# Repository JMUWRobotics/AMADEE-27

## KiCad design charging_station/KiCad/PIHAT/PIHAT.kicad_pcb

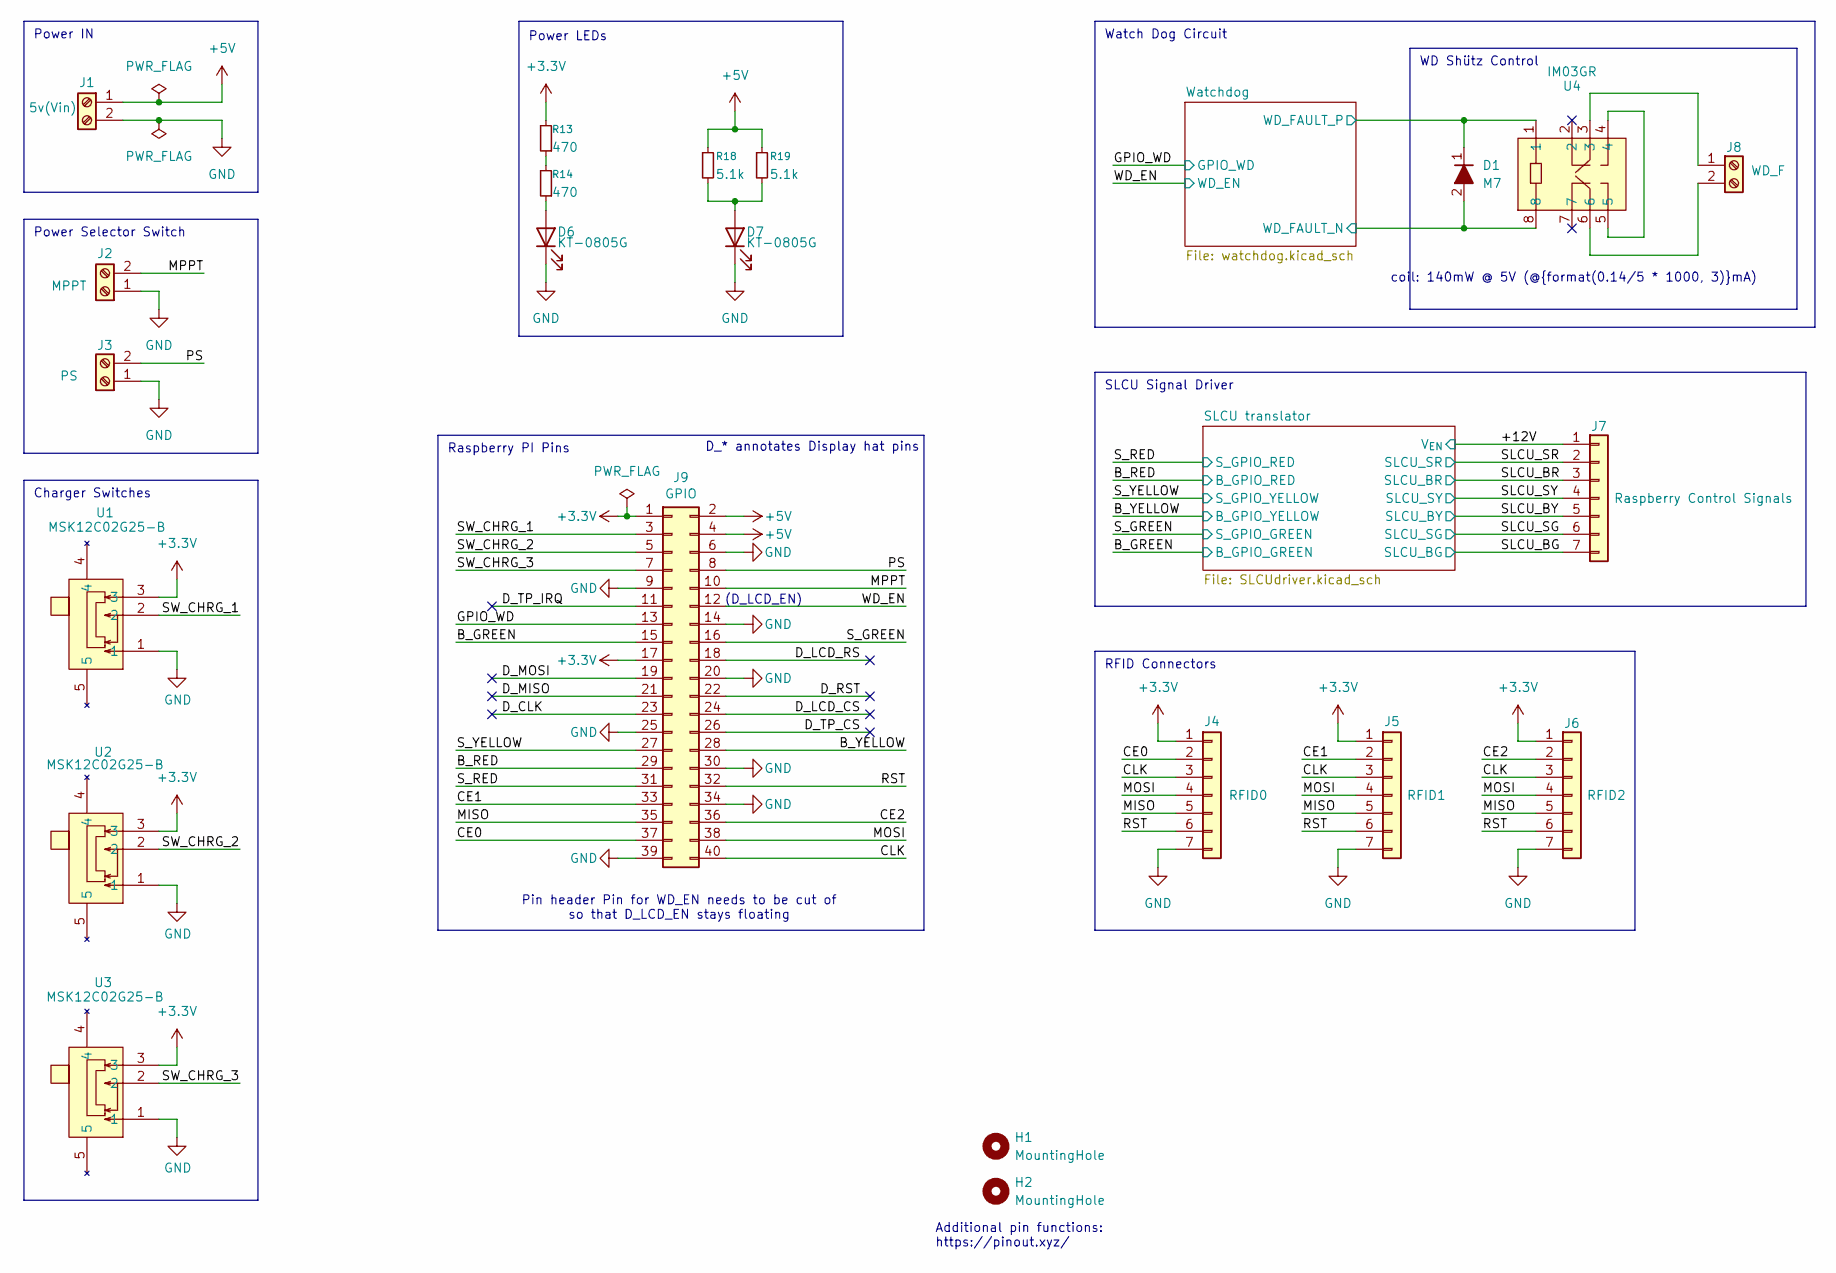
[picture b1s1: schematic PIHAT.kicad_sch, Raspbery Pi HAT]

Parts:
D1: M7; D_SMA; MPN M7; LCSC Part C95872
D6, D7: KT-0805G; LED_0805_2012Metric; MPN KT-0805G; LCSC Part C2297
H1: MountingHole; MountingHole_2.2mm_M2_DIN965_Pad
H2: MountingHole; MountingHole_2.5mm_Pad
J1: 5v(Vin); TerminalBlock_Phoenix_PT-1,5-2-5.0-H_1x02_P5.00mm_Horizontal; MPN 1935161; LCSC Part C3819953
J2: MPPT; TerminalBlock_Phoenix_PT-1,5-2-5.0-H_1x02_P5.00mm_Horizontal; MPN 1935161; LCSC Part C3819953
J3: PS; TerminalBlock_Phoenix_PT-1,5-2-5.0-H_1x02_P5.00mm_Horizontal; MPN 1935161; LCSC Part C3819953
J4: RFID0; JST_XH_S7B-XH-A_1x07_P2.50mm_Horizontal; MPN S7B-XH-A(LF)(SN); LCSC Part C157916
J5: RFID1; JST_XH_S7B-XH-A_1x07_P2.50mm_Horizontal; MPN S7B-XH-A(LF)(SN); LCSC Part C157916
J6: RFID2; JST_XH_S7B-XH-A_1x07_P2.50mm_Horizontal; MPN S7B-XH-A(LF)(SN); LCSC Part C157916
J7: Raspberry Control Signals; JST_XH_S7B-XH-A_1x07_P2.50mm_Horizontal; MPN S7B-XH-A(LF)(SN); LCSC Part C157916
J8: WD_F; TerminalBlock_Phoenix_PT-1,5-2-5.0-H_1x02_P5.00mm_Horizontal; MPN 1935161; LCSC Part C3819953
J9: GPIO; PinSocket_2x20_P2.54mm_Vertical; MPN SSQ-120-03-T-D; LCSC C6235776
R13, R14: 470; R_0603_1608Metric; LCSC C23179
R18, R19: 5.1k; R_0603_1608Metric; LCSC C17414
U1, U2, U3: MSK12C02G25-B; SW-SMD_MSK12C02G25-B; MPN MSK12C02G25-B; LCSC Part C22435663
U4: IM03GR; RELAY-SMD_IMXXGR; MPN IM03GR; LCSC Part C2153100

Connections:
+3.3V: J4.1, J5.1, J6.1, J9.1, J9.17, R13.2, U1.3, U2.3, U3.3; also elsewhere on the board
+5V: J1.1, J9.2, J9.4, R18.1, R19.1; also elsewhere on the board
/+12V: J7.1; also elsewhere on the board
/B_GREEN: J9.15; also elsewhere on the board
/B_RED: J9.29; also elsewhere on the board
/B_YELLOW: J9.28; also elsewhere on the board
/CE0: J4.2, J9.37
/CE1: J5.2, J9.33
/CE2: J6.2, J9.36
/CLK: J4.3, J5.3, J6.3, J9.40
/D_CLK: J9.23
/D_LCD_CS: J9.24
/D_LCD_RS: J9.18
/D_MISO: J9.21
/D_MOSI: J9.19
/D_RST: J9.22
/D_TP_CS: J9.26
/D_TP_IRQ: J9.11
/GPIO_WD: J9.13; also elsewhere on the board
/MISO: J4.5, J5.5, J6.5, J9.35
/MOSI: J4.4, J5.4, J6.4, J9.38
/MPPT: J2.2, J9.10
/PS: J3.2, J9.8
/RST: J4.6, J5.6, J6.6, J9.32
/SLCU_BG: J7.7; also elsewhere on the board
/SLCU_BR: J7.3; also elsewhere on the board
/SLCU_BY: J7.5; also elsewhere on the board
/SLCU_SG: J7.6; also elsewhere on the board
/SLCU_SR: J7.2; also elsewhere on the board
/SLCU_SY: J7.4; also elsewhere on the board
/SW_CHRG_1: J9.3, U1.2
/SW_CHRG_2: J9.5, U2.2
/SW_CHRG_3: J9.7, U3.2
/S_GREEN: J9.16; also elsewhere on the board
/S_RED: J9.31; also elsewhere on the board
/S_YELLOW: J9.27; also elsewhere on the board
/WD_EN: J9.12; also elsewhere on the board
/Watchdog/WD_FAULT_N: D1.2 (A), U4.8; also elsewhere on the board
/Watchdog/WD_FAULT_P: D1.1 (K), U4.1; also elsewhere on the board
GND: D6.1 (K), D7.1 (K), J1.2, J2.1, J3.1, J4.7, J5.7, J6.7, J9.6, J9.9, J9.14, J9.20, J9.25, J9.30, J9.34, J9.39, U1.1, U2.1, U3.1; also elsewhere on the board
unnamed: D6.2 (A), R14.1
unnamed: D7.2 (A), R18.2, R19.2
unnamed: J8.1, U4.3
unnamed: J8.2, U4.6
unnamed: R13.1, R14.2
unnamed: U4.4, U4.5

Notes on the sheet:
Raspberry PI Pins
(D_LCD_EN)
Additional pin functions: https://pinout.xyz/
SLCU Signal Driver
RFID Connectors
WD Shütz Control
Pin header Pin for WD_EN needs to be cut of so that D_LCD_EN stays floating
Power Selector Switch
Watch Dog Circuit
Power LEDs
Charger Switches
Power IN
coil: 140mW @ 5V (@{format(0.14/5 * 1000, 3)}mA)
D_* annotates Display hat pins

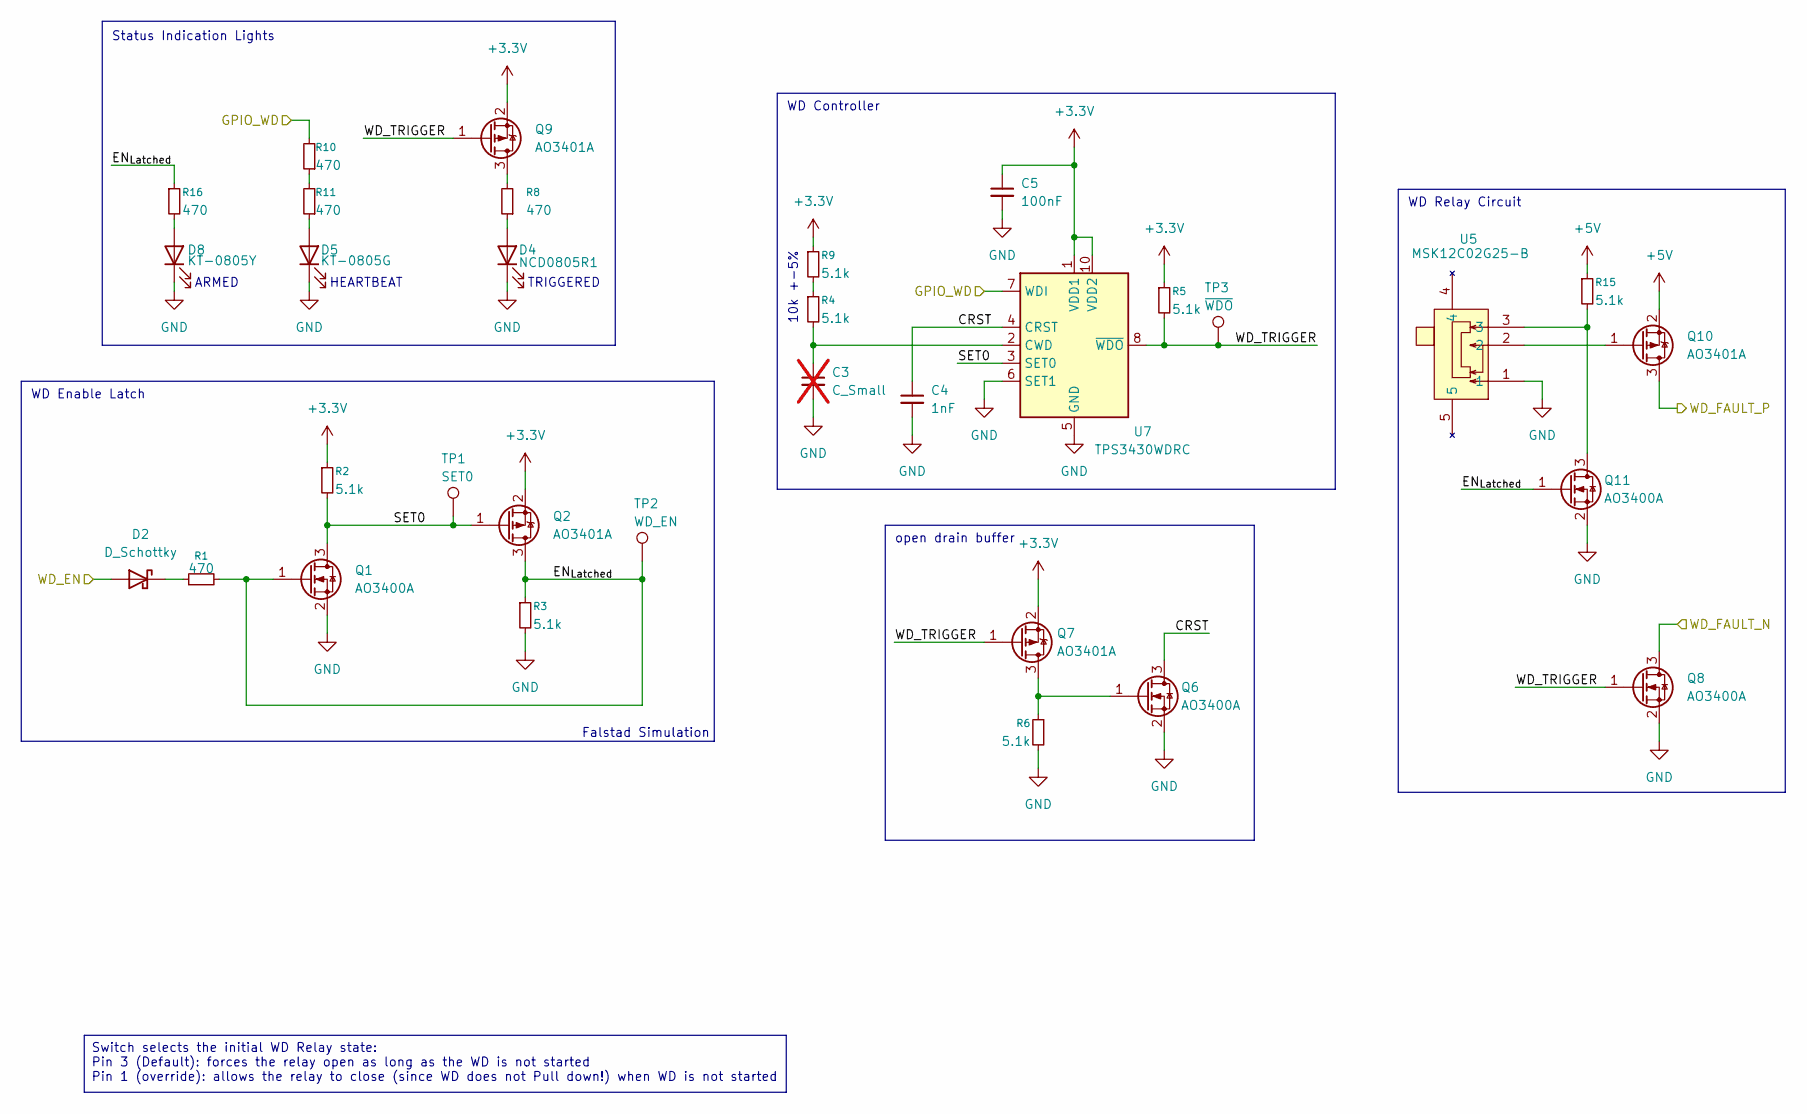
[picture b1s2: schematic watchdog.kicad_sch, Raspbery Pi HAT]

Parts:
C3: C_Small; C_0805_2012Metric_Pad1.18x1.45mm_HandSolder; not fitted
C4: 1nF; C_0603_1608Metric
C5: 100nF; C_0603_1608Metric; LCSC Part C14663
D2: D_Schottky; D_SOD-323
D4: NCD0805R1; LED_0805_2012Metric; MPN NCD0805R1; LCSC Part C84256
D5: KT-0805G; LED_0805_2012Metric; MPN KT-0805G; LCSC Part C2297
D8: KT-0805Y; LED_0805_2012Metric; MPN KT-0805Y; LCSC Part C2296
Q1, Q6, Q8, Q11: AO3400A; SOT-23; MPN AO3400A; LCSC Part C15127
Q2, Q7, Q9, Q10: AO3401A; SOT-23; MPN AO3401A; LCSC Part C15127
R1, R8, R10, R11, R16: 470; R_0603_1608Metric; LCSC C23179
R2, R3, R4, R5, R6, R9, R15: 5.1k; R_0603_1608Metric; LCSC C17414
TP1: SET0; TestPoint_Pad_D1.0mm
TP2: WD_EN; TestPoint_Pad_D1.0mm
TP3: ~{WDO}; TestPoint_Pad_D1.0mm
U5: MSK12C02G25-B; SW-SMD_MSK12C02G25-B; MPN MSK12C02G25-B; LCSC Part C22435663
U7: TPS3430WDRC; VSON-10-1EP_3x3mm_P0.5mm_EP1.65x2.4mm

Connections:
+3.3V: C5.1, Q2.2 (S), Q7.2 (S), Q9.2 (S), R2.1, R5.1, R9.1, U7.1 (VDD1), U7.10 (VDD2); also elsewhere on the board
+5V: Q10.2 (S), R15.1; also elsewhere on the board
/GPIO_WD: R10.2, U7.7 (WDI); also elsewhere on the board
/WD_EN: D2.2 (A); also elsewhere on the board
/Watchdog/CRST: C4.1, Q6.3 (D), U7.4 (CRST)
/Watchdog/EN_{Latched}: Q1.1 (G), Q2.3 (D), Q11.1 (G), R1.2, R3.1, R16.1, TP2.1 (1_1)
/Watchdog/SET0: Q1.3 (D), Q2.1 (G), R2.2, TP1.1 (1_1), U7.3 (SET0)
/Watchdog/WD_FAULT_N: Q8.3 (D); also elsewhere on the board
/Watchdog/WD_FAULT_P: Q10.3 (D); also elsewhere on the board
/Watchdog/WD_TRIGGER: Q7.1 (G), Q8.1 (G), Q9.1 (G), R5.2, TP3.1 (1_1), U7.8 (~WDO)
GND: C3.2, C4.2, C5.2, D4.1 (K), D5.1 (K), D8.1 (K), Q1.2 (S), Q6.2 (S), Q8.2 (S), Q11.2 (S), R3.2, R6.2, U5.1, U7.5 (GND), U7.6 (SET1), U7.11 (GND); also elsewhere on the board
unnamed: D2.1 (K), R1.1
unnamed: D4.2 (A), R8.1
unnamed: D5.2 (A), R11.1
unnamed: D8.2 (A), R16.2
unnamed: Q6.1 (G), Q7.3 (D), R6.1
unnamed: Q9.3 (D), R8.2
unnamed: Q10.1 (G), U5.2
unnamed: Q11.3 (D), R15.2, U5.3
unnamed: R4.1, R9.2
unnamed: R10.1, R11.2
unnamed: C3.1, R4.2, U7.2 (CWD)

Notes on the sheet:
HEARTBEAT
open drain buffer
10k +-5%
Falstad Simulation
WD Enable Latch
TRIGGERED
Status Indication Lights
ARMED
WD Controller
WD Relay Circuit
Switch selects the initial WD Relay state: Pin 3 (Default): forces the relay open as long as the WD is not started Pin 1 (override): allows the relay to close (since WD does not Pull down!) when WD is not started

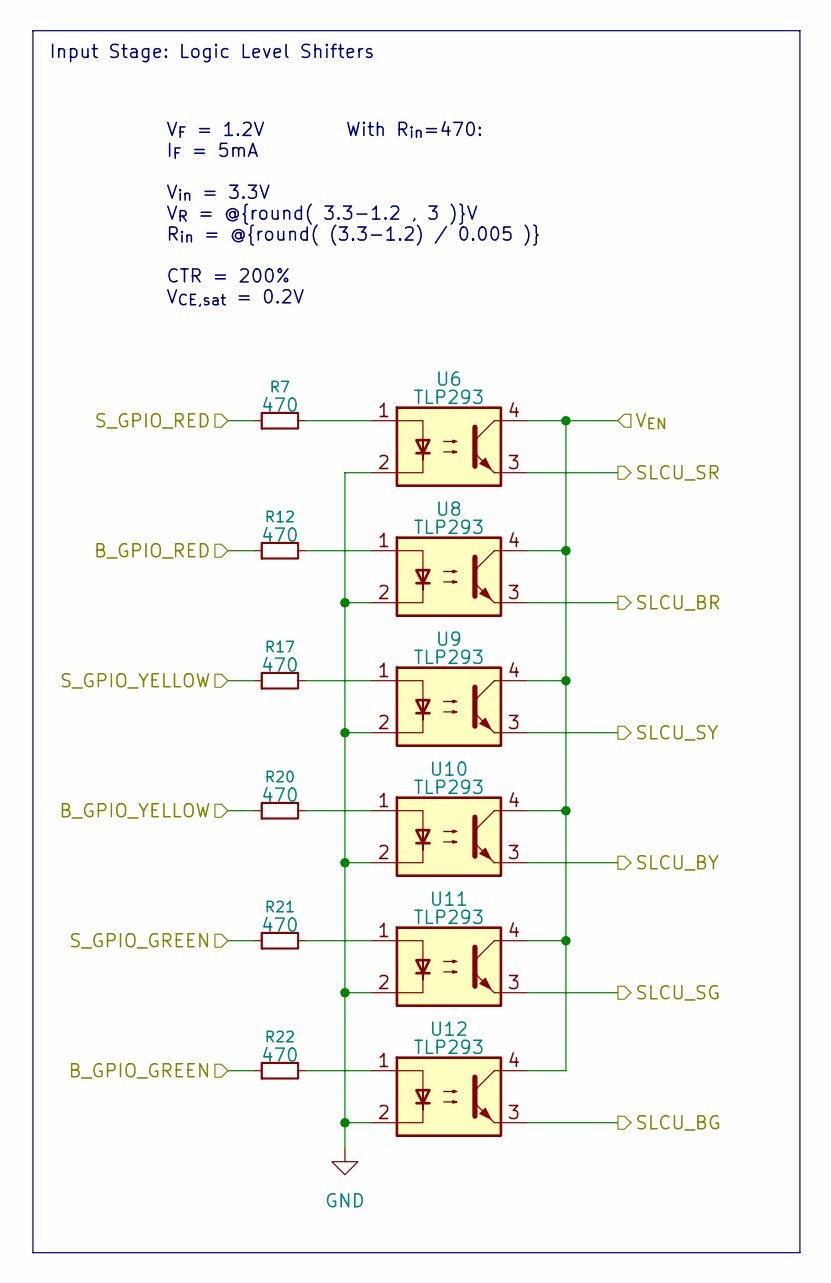
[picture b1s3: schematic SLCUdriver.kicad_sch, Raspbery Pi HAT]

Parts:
R7, R12, R17, R20, R21, R22: 470; R_0603_1608Metric; LCSC C23179
U6, U8, U9, U10, U11, U12: TLP293; SOIC-4_4.55x2.6mm_P1.27mm; MPN TLP293(BLL-TPL,E; LCSC C3008594

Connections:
/+12V: U6.4, U8.4, U9.4, U10.4, U11.4, U12.4; also elsewhere on the board
/B_GREEN: R22.1; also elsewhere on the board
/B_RED: R12.1; also elsewhere on the board
/B_YELLOW: R20.1; also elsewhere on the board
/SLCU_BG: U12.3; also elsewhere on the board
/SLCU_BR: U8.3; also elsewhere on the board
/SLCU_BY: U10.3; also elsewhere on the board
/SLCU_SG: U11.3; also elsewhere on the board
/SLCU_SR: U6.3; also elsewhere on the board
/SLCU_SY: U9.3; also elsewhere on the board
/S_GREEN: R21.1; also elsewhere on the board
/S_RED: R7.1; also elsewhere on the board
/S_YELLOW: R17.1; also elsewhere on the board
GND: U6.2, U8.2, U9.2, U10.2, U11.2, U12.2; also elsewhere on the board
unnamed: R7.2, U6.1
unnamed: R12.2, U8.1
unnamed: R17.2, U9.1
unnamed: R20.2, U10.1
unnamed: R21.2, U11.1
unnamed: R22.2, U12.1

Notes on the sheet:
With R_{in}=470:
V_{F} = 1.2V I_{F} = 5mA V_{in} = 3.3V V_{R} = @{round( 3.3-1.2 , 3 )}V R_{in} = @{round( (3.3-1.2) / 0.005 )} CTR = 200% V_{CE,sat} = 0.2V
Input Stage: Logic Level Shifters

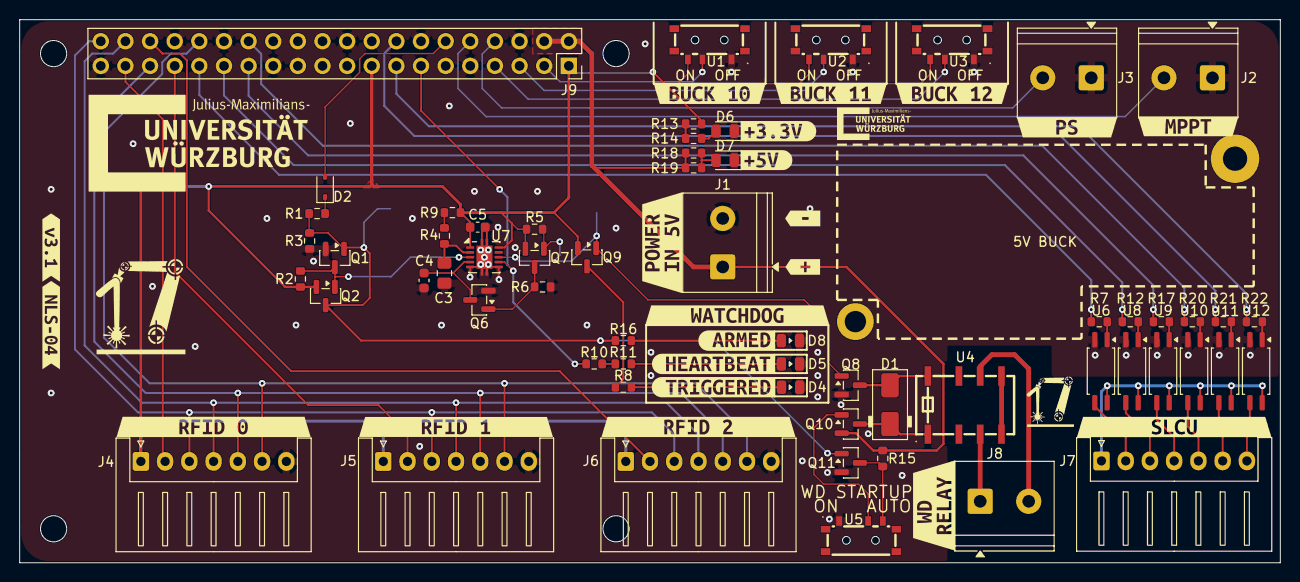
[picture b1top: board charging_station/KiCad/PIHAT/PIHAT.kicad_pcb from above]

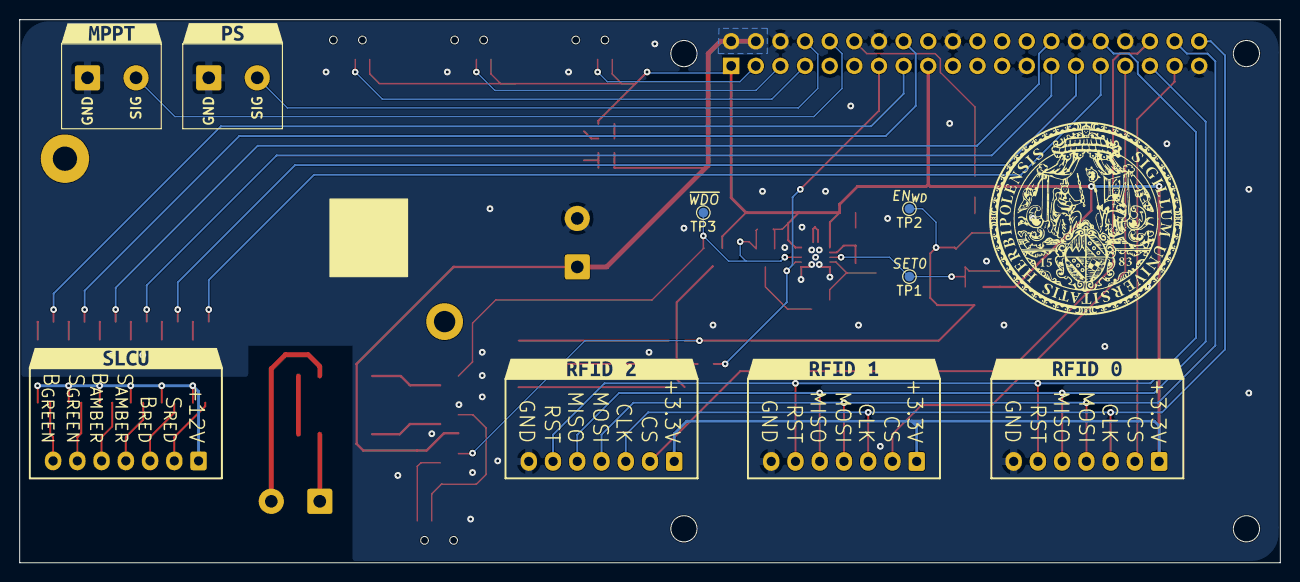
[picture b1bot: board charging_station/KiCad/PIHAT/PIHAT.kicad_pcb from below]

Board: 2 copper layers, 130.0 x 56.0 mm, 97 parts (13 on the bottom side), 59 nets.

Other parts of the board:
MH1, MH2, MH3, MH4: MountingHole_2.7mm_M2.5
kibuzzard-6AD53C3D: G***; kibuzzard-6AD53C3D
kibuzzard-6AD53C20, kibuzzard-6AD53C20#2: G***; kibuzzard-6AD53C20
kibuzzard-6AD53C43: G***; kibuzzard-6AD53C43
kibuzzard-6AD53C84: G***; kibuzzard-6AD53C84
kibuzzard-6AD53CF1: G***; kibuzzard-6AD53CF1
kibuzzard-6AD53D49: G***; kibuzzard-6AD53D49
kibuzzard-6AD53DF3: G***; kibuzzard-6AD53DF3
kibuzzard-6AD53E3A: G***; kibuzzard-6AD53E3A
kibuzzard-6AD53E40: G***; kibuzzard-6AD53E40
kibuzzard-6AD530C8: G***; kibuzzard-6AD530C8
kibuzzard-6AD530EA: G***; kibuzzard-6AD530EA
kibuzzard-6AD537E7: G***; kibuzzard-6AD537E7
kibuzzard-6AD540AE: G***; kibuzzard-6AD540AE
kibuzzard-6AD541D1: G***; kibuzzard-6AD541D1
kibuzzard-6AD543B1: G***; kibuzzard-6AD543B1
kibuzzard-6AD543B7: G***; kibuzzard-6AD543B7
kibuzzard-6AD554A5: G***; kibuzzard-6AD554A5
kibuzzard-6AD5310E: G***; kibuzzard-6AD5310E
kibuzzard-6AD5403C: G***; kibuzzard-6AD5403C
kibuzzard-6AD54089: G***; kibuzzard-6AD54089
kibuzzard-6AF5E61E: G***; kibuzzard-6AF5E61E
kibuzzard-6AF5E623: G***; kibuzzard-6AF5E623
kibuzzard-6AF5EA3F: G***; kibuzzard-6AF5EA3F
kibuzzard-6AF5F1CD: G***; kibuzzard-6AF5F1CD
kibuzzard-6AF5F1D2: G***; kibuzzard-6AF5F1D2
kibuzzard-6AF35593: G***; kibuzzard-6AF35593

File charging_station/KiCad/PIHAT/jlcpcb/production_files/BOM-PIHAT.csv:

Comment,Designator,Footprint,LCSC,Quantity
100nF,C5,C_0603_1608Metric,C14663,1
1nF,C4,C_0603_1608Metric,C1588,1
470,"R1,R10,R11,R12,R13,R14,R16,R17,R20,R21,R22,R7,R8",R_0603_1608Metric,C23179,13
5.1k,"R15,R18,R19,R2,R3,R4,R5,R6,R9",R_0603_1608Metric,C23186,9
5v(Vin),J1,"TerminalBlock_Phoenix_PT-1,5-2-5.0-H_1x02_P5.00mm_Horizontal",C3819953,1
AO3400A,"Q1,Q11,Q6,Q8",SOT-23,C20917,4
AO3401A,"Q10,Q2,Q7,Q9",SOT-23,C15127,4
D_Schottky,D2,D_SOD-323,C7420360,1
GPIO,J9,PinSocket_2x20_P2.54mm_Vertical,C6235776,1
IM03GR,U4,RELAY-SMD_IMXXGR,C2153100,1
KT-0805G,"D5,D6,D7",LED_0805_2012Metric,C2297,3
KT-0805Y,D8,LED_0805_2012Metric,C2296,1
M7,D1,D_SMA,C95872,1
MPPT,J2,"TerminalBlock_Phoenix_PT-1,5-2-5.0-H_1x02_P5.00mm_Horizontal",C3819953,1
MSK12C02G25-B,"U1,U2,U3,U5",SW-SMD_MSK12C02G25-B,C22435663,4
NCD0805R1,D4,LED_0805_2012Metric,C84256,1
PS,J3,"TerminalBlock_Phoenix_PT-1,5-2-5.0-H_1x02_P5.00mm_Horizontal",C3819953,1
RFID0,J4,JST_XH_S7B-XH-A_1x07_P2.50mm_Horizontal,C157916,1
RFID1,J5,JST_XH_S7B-XH-A_1x07_P2.50mm_Horizontal,C157916,1
RFID2,J6,JST_XH_S7B-XH-A_1x07_P2.50mm_Horizontal,C157916,1
Raspberry Control Signals,J7,JST_XH_S7B-XH-A_1x07_P2.50mm_Horizontal,C157916,1
TLP293,"U10,U11,U12,U6,U8,U9",SOIC-4_4.55x2.6mm_P1.27mm,C3008594,6
TPS3430WDRC,U7,VSON-10-1EP_3x3mm_P0.5mm_EP1.65x2.4mm,C2870545,1
WD_F,J8,"TerminalBlock_Phoenix_PT-1,5-2-5.0-H_1x02_P5.00mm_Horizontal",C3819953,1

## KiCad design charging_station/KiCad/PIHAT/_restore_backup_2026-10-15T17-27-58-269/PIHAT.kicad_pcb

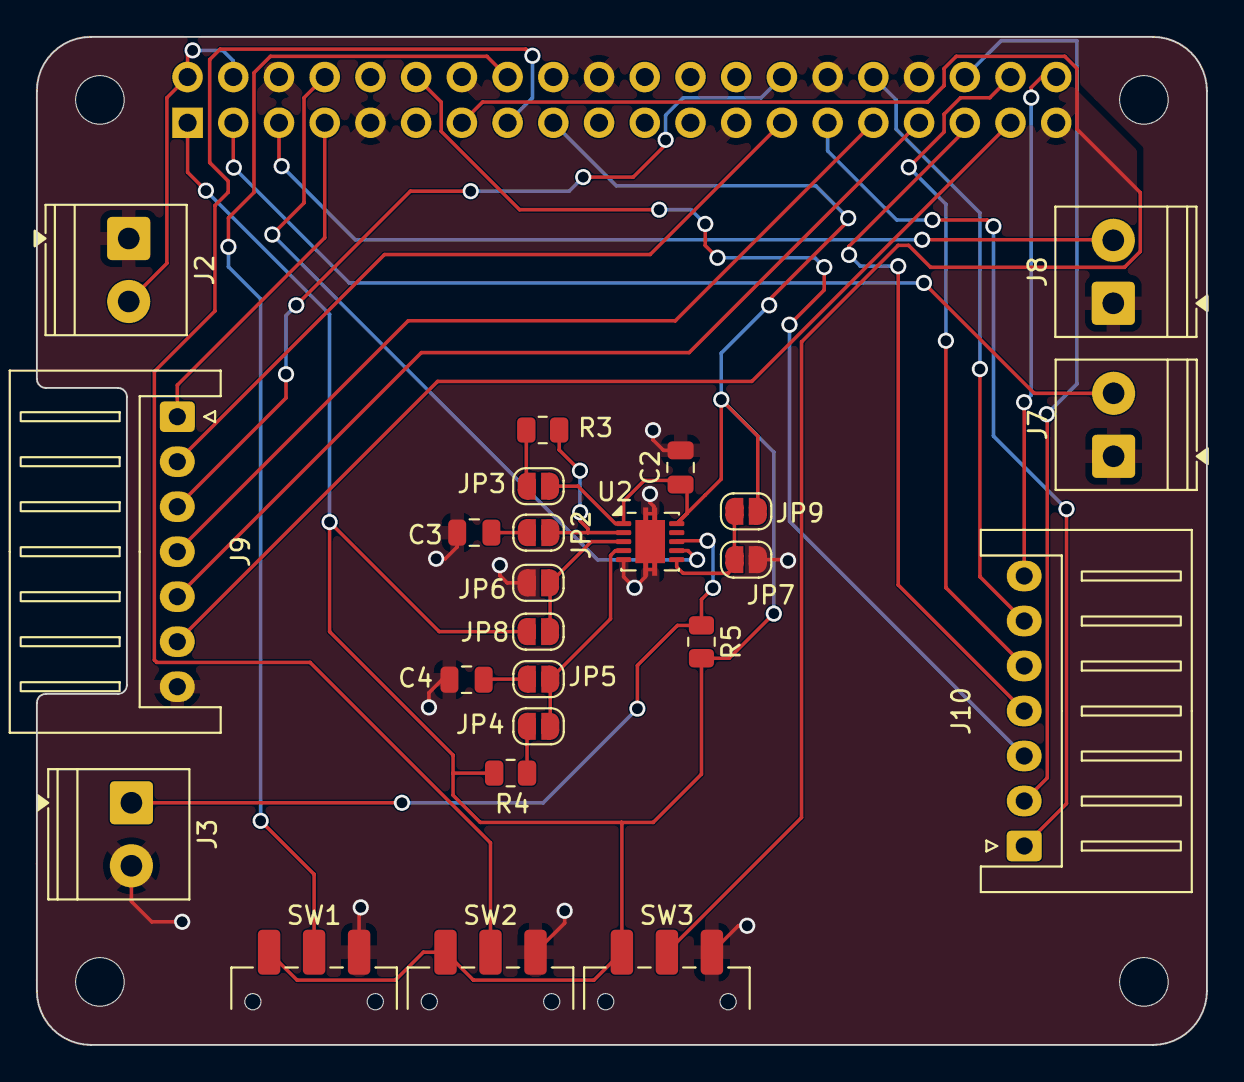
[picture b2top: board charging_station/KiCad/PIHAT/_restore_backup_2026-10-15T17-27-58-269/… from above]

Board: 2 copper layers, 65.0 x 56.0 mm, 29 parts (1 on the bottom side), 31 nets.

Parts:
C2: 100nf; C_0805_2012Metric
C3, C4: C; C_0805_2012Metric
J1: GPIO; PinSocket_2x20_P2.54mm_Vertical
J2: 5v(Vin); TerminalBlock_Phoenix_PT-1,5-2-3.5-H_1x02_P3.50mm_Horizontal
J3: WD_F; TerminalBlock_Phoenix_PT-1,5-2-3.5-H_1x02_P3.50mm_Horizontal
J7: MPPT; TerminalBlock_Phoenix_PT-1,5-2-3.5-H_1x02_P3.50mm_Horizontal
J8: PS; TerminalBlock_Phoenix_PT-1,5-2-3.5-H_1x02_P3.50mm_Horizontal
J9: Stack light; JST_XH_S7B-XH-A_1x07_P2.50mm_Horizontal
J10: RFID; JST_XH_S7B-XH-A_1x07_P2.50mm_Horizontal
JP2, JP3, JP4, JP5, JP6, JP7, JP8, JP9: SolderJumper_2_Open; SolderJumper-2_P1.3mm_Open_RoundedPad1.0x1.5mm
MH1, MH2, MH3, MH4: MountingHole_2.7mm_M2.5
R3, R5: 10k; R_0805_2012Metric
R4: R; R_0805_2012Metric
SW1, SW2, SW3: Sw_1; SW_SPDT_CK_JS102011SAQN
U2: TPS3430WDRC; VSON-10-1EP_3x3mm_P0.5mm_EP1.65x2.4mm

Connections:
/Raspi5/3v3: C2.1, J1.1, J1.17, JP3.1 (A), JP8.2 (B), JP9.2 (B), R4.1, R5.2, SW1.1, SW2.1, SW3.1, U2.1 (VDD1), U2.10 (VDD2)
/Raspi5/5v: J1.2, J1.4, J2.2
/Raspi5/GPIO0/R_MO: J1.27, J9.2
/Raspi5/GPIO1/Y_ST: J1.28, J9.3
/Raspi5/GPIO2/MPPT: J1.3, J7.2
/Raspi5/GPIO3/PS: J1.5, J8.2
/Raspi5/GPIO4/R_ST: J1.7, J9.1
/Raspi5/GPIO5/CE1: J1.29, J10.1
/Raspi5/GPIO6/Y_MO: J1.31, J9.4
/Raspi5/GPIO12/RST: J1.32, J10.6
/Raspi5/GPIO13/G_ST: J1.33, J9.5
/Raspi5/GPIO14/GPIO_WD: J1.8, U2.7 (WDI)
/Raspi5/GPIO16/CE2: J1.36, J10.2
/Raspi5/GPIO18/CE0: J1.12, J10.3
/Raspi5/GPIO19/MISO: J1.35, J10.4
/Raspi5/GPIO20/MOSI: J1.38, J10.5
/Raspi5/GPIO21/CLK: J1.40, J10.7
/Raspi5/GPIO22: J1.15, SW2.2 (3)
/Raspi5/GPIO23: J1.16, SW1.2 (3)
/Raspi5/GPIO26/G_MO: J1.37, J9.6
/Raspi5/GPIO27: J1.13, SW3.2 (3)
/Watchdog/WD_FAULT: J3.1, R5.1, U2.8 (~WDO)
GND: C2.2, C3.1, C4.1, J1.6, J1.9, J1.14, J1.20, J1.25, J1.30, J1.34, J1.39, J2.1, J3.2, J7.1, J8.1, J9.7, JP6.1 (A), JP7.1 (A), SW1.3 (4), SW2.3 (4), SW3.3 (4), U2.5 (GND), U2.11 (GND)
unnamed: C3.2, JP2.1 (A)
unnamed: JP2.2 (B), R3.1, U2.2 (CWD)
unnamed: JP3.2 (B), R3.2
unnamed: JP4.1 (A), JP5.2 (B), U2.4 (CRST)
unnamed: JP4.2 (B), R4.2
unnamed: C4.2, JP5.1 (A)
unnamed: JP6.2 (B), JP8.1 (A), U2.3 (SET0)
unnamed: JP7.2 (B), JP9.1 (A), U2.6 (SET1)

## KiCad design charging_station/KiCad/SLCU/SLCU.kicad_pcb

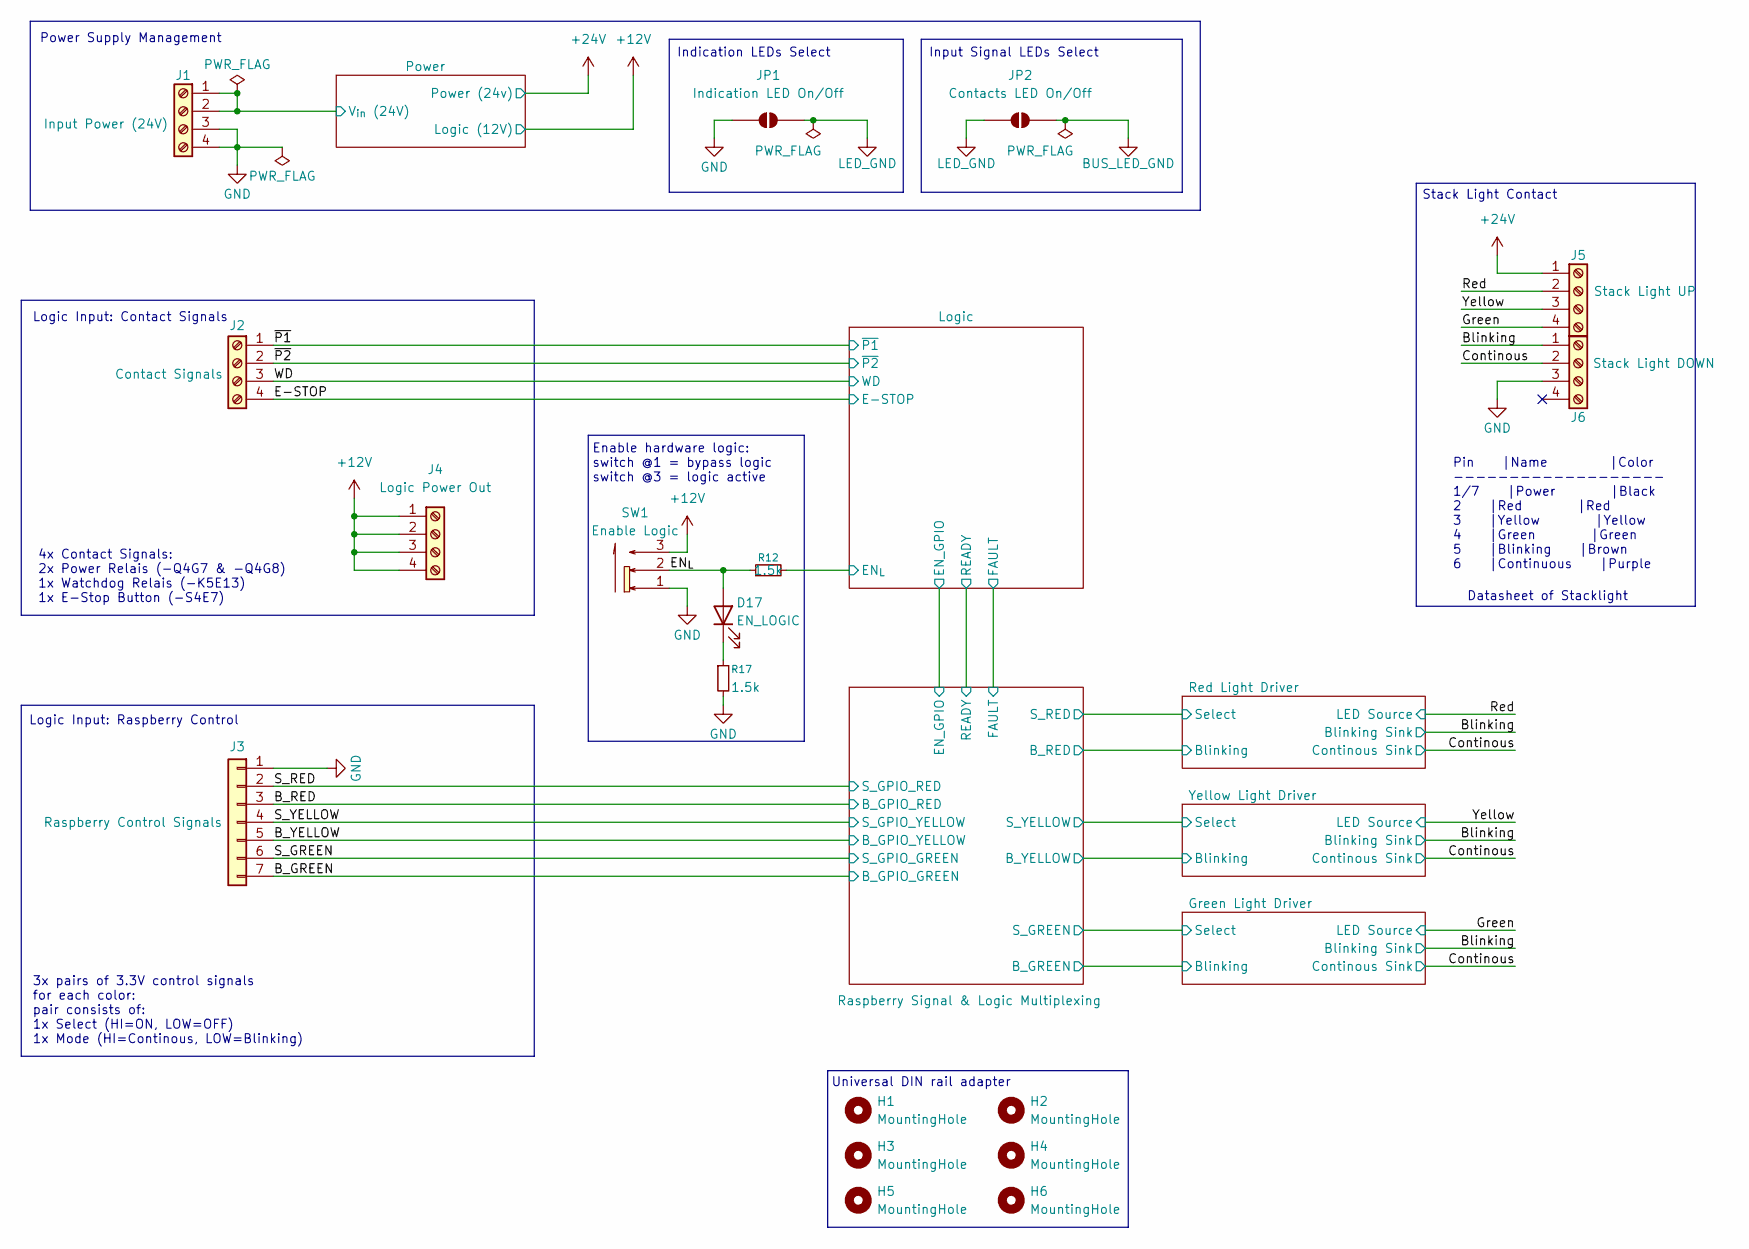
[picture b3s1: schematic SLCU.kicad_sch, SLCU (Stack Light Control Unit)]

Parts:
D17: EN_LOGIC; LED_0805_2012Metric_Pad1.15x1.40mm_HandSolder
H1, H2, H3, H4, H5, H6: MountingHole; MountingHole_3.2mm_M3
J1: Input Power (24V); TerminalBlock_Phoenix_MKDS-1,5-4_1x04_P5.00mm_Horizontal; MPN 1935187; LCSC Part C3817931
J2: Contact Signals; TerminalBlock_Phoenix_MKDS-1,5-4_1x04_P5.00mm_Horizontal; MPN 1935187; LCSC Part C3817931
J3: Raspberry Control Signals; JST_XH_S7B-XH-A_1x07_P2.50mm_Horizontal; MPN S7B-XH-A(LF)(SN); LCSC Part C157916
J4: Logic Power Out; TerminalBlock_Phoenix_MKDS-1,5-4_1x04_P5.00mm_Horizontal; MPN 1935187; LCSC Part C3817931
J5: Stack Light UP; TerminalBlock_Phoenix_MKDS-1,5-4_1x04_P5.00mm_Horizontal; MPN 1935187; LCSC Part C3817931
J6: Stack Light DOWN; TerminalBlock_Phoenix_MKDS-1,5-4_1x04_P5.00mm_Horizontal; MPN 1935187; LCSC Part C3817931
JP1: Indication LED On/Off; SolderJumper-2_P1.3mm_Open_RoundedPad1.0x1.5mm
JP2: Contacts LED On/Off; SolderJumper-2_P1.3mm_Open_RoundedPad1.0x1.5mm
R12, R17: 1.5k; R_0805_2012Metric_Pad1.20x1.40mm_HandSolder
SW1: Enable Logic; SW-SMD_SHOUHAN_MST-22D18G23J_C2875122; MPN MST-22D18G2 3J; LCSC Part C2875122

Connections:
+12V: J4.1, J4.2, J4.3, J4.4, SW1.3; also elsewhere on the board
+24V: J5.1; also elsewhere on the board
/B_GREEN: J3.7; also elsewhere on the board
/B_RED: J3.3; also elsewhere on the board
/B_YELLOW: J3.5; also elsewhere on the board
/Blinking: J6.1; also elsewhere on the board
/Continous: J6.2; also elsewhere on the board
/E-STOP: J2.4; also elsewhere on the board
/EN_{L}: D17.2 (A), R12.1, SW1.2
/Green: J5.4; also elsewhere on the board
/Logic/EN_{L}: R12.2; also elsewhere on the board
/Power/V_{in} (24V): J1.1, J1.2; also elsewhere on the board
/Red: J5.2; also elsewhere on the board
/S_GREEN: J3.6; also elsewhere on the board
/S_RED: J3.2; also elsewhere on the board
/S_YELLOW: J3.4; also elsewhere on the board
/WD: J2.3; also elsewhere on the board
/Yellow: J5.3; also elsewhere on the board
/~P1: J2.1; also elsewhere on the board
/~P2: J2.2; also elsewhere on the board
BUS_LED_GND: JP2.2 (B); also elsewhere on the board
GND: J1.3, J1.4, J3.1, J6.3, JP1.1 (A), R17.2, SW1.1; also elsewhere on the board
LED_GND: JP1.2 (B), JP2.1 (A); also elsewhere on the board
unnamed: D17.1 (K), R17.1

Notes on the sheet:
Input Signal LEDs Select
Enable hardware logic: switch @1 = bypass logic switch @3 = logic active
Logic Input: Raspberry Control
Power Supply Management
Indication LEDs Select
Datasheet of Stacklight
Pin |Name |Color ------------------- 1/7 |Power |Black 2 |Red |Red 3 |Yellow |Yellow 4 |Green |Green 5 |Blinking |Brown 6 |Continuous |Purple
Logic Input: Contact Signals
3x pairs of 3.3V control signals for each color: pair consists of: 1x Select (HI=ON, LOW=OFF) 1x Mode (HI=Continous, LOW=Blinking)
Stack Light Contact
Universal DIN rail adapter
4x Contact Signals: 2x Power Relais (-Q4G7 & -Q4G8) 1x Watchdog Relais (-K5E13) 1x E-Stop Button (-S4E7)

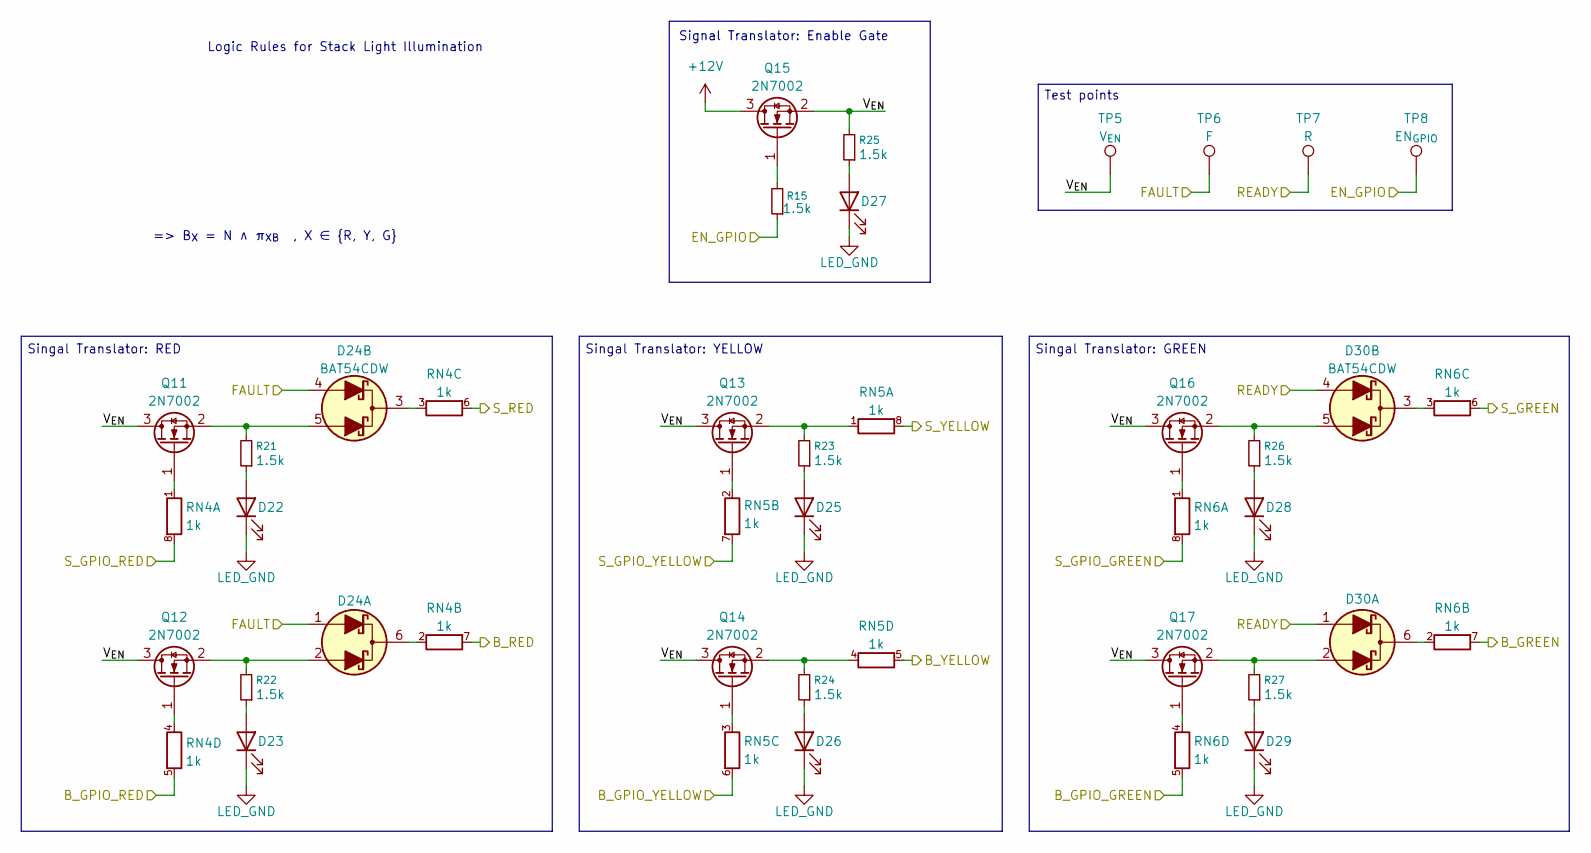
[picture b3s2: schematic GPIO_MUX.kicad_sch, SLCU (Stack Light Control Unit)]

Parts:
D22, D23, D25, D26, D27, D28, D29: LED; LED_0805_2012Metric_Pad1.15x1.40mm_HandSolder
D24, D30: BAT54CDW; SOT-363_SC-70-6
Q11, Q12, Q13, Q14, Q15, Q16, Q17: 2N7002; SOT-323_SC-70
R15, R21, R22, R23, R24, R25, R26, R27: 1.5k; R_0805_2012Metric_Pad1.20x1.40mm_HandSolder
RN4, RN5, RN6: 1k; RES-ARRAY-SMD_0603-8P-L3.2-W1.6-BL; MPN 4D03WGJ0102T5E; LCSC Part C20197
TP5: V_{EN}; TestPoint_Pad_D1.0mm
TP6: F; TestPoint_Pad_D1.0mm
TP7: R; TestPoint_Pad_D1.0mm
TP8: EN_{GPIO}; TestPoint_Pad_D1.0mm

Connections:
+12V: Q15.3 (D); also elsewhere on the board
/B_GREEN: RN6.5 (R4.2); also elsewhere on the board
/B_RED: RN4.5 (R4.2); also elsewhere on the board
/B_YELLOW: RN5.6 (R3.2); also elsewhere on the board
/Green Light Driver/Blinking: RN6.7 (R2.2); also elsewhere on the board
/Green Light Driver/Select: RN6.6 (R3.2); also elsewhere on the board
/Logic/EN_GPIO: R15.1, TP8.1 (1_1); also elsewhere on the board
/Logic/FAULT: D24.1 (A1), D24.4 (A2), TP6.1 (1_1); also elsewhere on the board
/Logic/READY: D30.1 (A1), D30.4 (A2), TP7.1 (1_1); also elsewhere on the board
/Raspberry Signal & Logic Multiplexing/B_RED: RN4.7 (R2.2); also elsewhere on the board
/Raspberry Signal & Logic Multiplexing/B_YELLOW: RN5.5 (R4.2); also elsewhere on the board
/Raspberry Signal & Logic Multiplexing/S_RED: RN4.6 (R3.2); also elsewhere on the board
/Raspberry Signal & Logic Multiplexing/S_YELLOW: RN5.8 (R1.2); also elsewhere on the board
/Raspberry Signal & Logic Multiplexing/V_{EN}: Q11.3 (D), Q12.3 (D), Q13.3 (D), Q14.3 (D), Q15.2 (S), Q16.3 (D), Q17.3 (D), R25.2, TP5.1 (1_1)
/S_GREEN: RN6.8 (R1.2); also elsewhere on the board
/S_RED: RN4.8 (R1.2); also elsewhere on the board
/S_YELLOW: RN5.7 (R2.2); also elsewhere on the board
LED_GND: D22.1 (K), D23.1 (K), D25.1 (K), D26.1 (K), D27.1 (K), D28.1 (K), D29.1 (K); also elsewhere on the board
unnamed: D22.2 (A), R21.1
unnamed: D23.2 (A), R22.1
unnamed: D24.6 (K1), RN4.2 (R2.1)
unnamed: D24.3 (K2), RN4.3 (R3.1)
unnamed: D25.2 (A), R23.1
unnamed: D26.2 (A), R24.1
unnamed: D27.2 (A), R25.1
unnamed: D28.2 (A), R26.1
unnamed: D29.2 (A), R27.1
unnamed: D30.6 (K1), RN6.2 (R2.1)
unnamed: D30.3 (K2), RN6.3 (R3.1)
unnamed: Q11.1 (G), RN4.1 (R1.1)
unnamed: D24.5 (A2), Q11.2 (S), R21.2
unnamed: Q12.1 (G), RN4.4 (R4.1)
unnamed: D24.2 (A1), Q12.2 (S), R22.2
unnamed: Q13.1 (G), RN5.2 (R2.1)
unnamed: Q13.2 (S), R23.2, RN5.1 (R1.1)
unnamed: Q14.1 (G), RN5.3 (R3.1)
unnamed: Q14.2 (S), R24.2, RN5.4 (R4.1)
unnamed: Q15.1 (G), R15.2
unnamed: Q16.1 (G), RN6.1 (R1.1)
unnamed: D30.5 (A2), Q16.2 (S), R26.2
unnamed: Q17.1 (G), RN6.4 (R4.1)
unnamed: D30.2 (A1), Q17.2 (S), R27.2

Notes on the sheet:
Singal Translator: GREEN
Signal Translator: Enable Gate
Singal Translator: YELLOW
=> B_{X} = N ∧ π_{XB} , X ∈ {R, Y, G}
Test points
Singal Translator: RED
Logic Rules for Stack Light Illumination
